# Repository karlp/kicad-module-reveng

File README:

Contains kicad projects used to generate rough 3d models for various modules.

The schematics are _very_ not clean, they're just enough to get all the right footprints so that kicad can autogenerate a nice 3d model for me.

Each directory should have it's own readme

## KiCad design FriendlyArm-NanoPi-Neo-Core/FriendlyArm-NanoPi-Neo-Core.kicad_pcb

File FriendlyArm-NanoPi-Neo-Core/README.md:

## physical model of NanoPi Neo Core

A "schematic" and "layout" that is _only_ intended to capture the
physical properties, making it easier to 3d model.

The usb connector and sd card connector and leds are all
not entirely _correct_ but are representitive, and placed appropriately.

Sources:
http://wiki.friendlyarm.com/wiki/index.php/NanoPi_NEO_Core

## Preview 
Examples of how it looks right now....

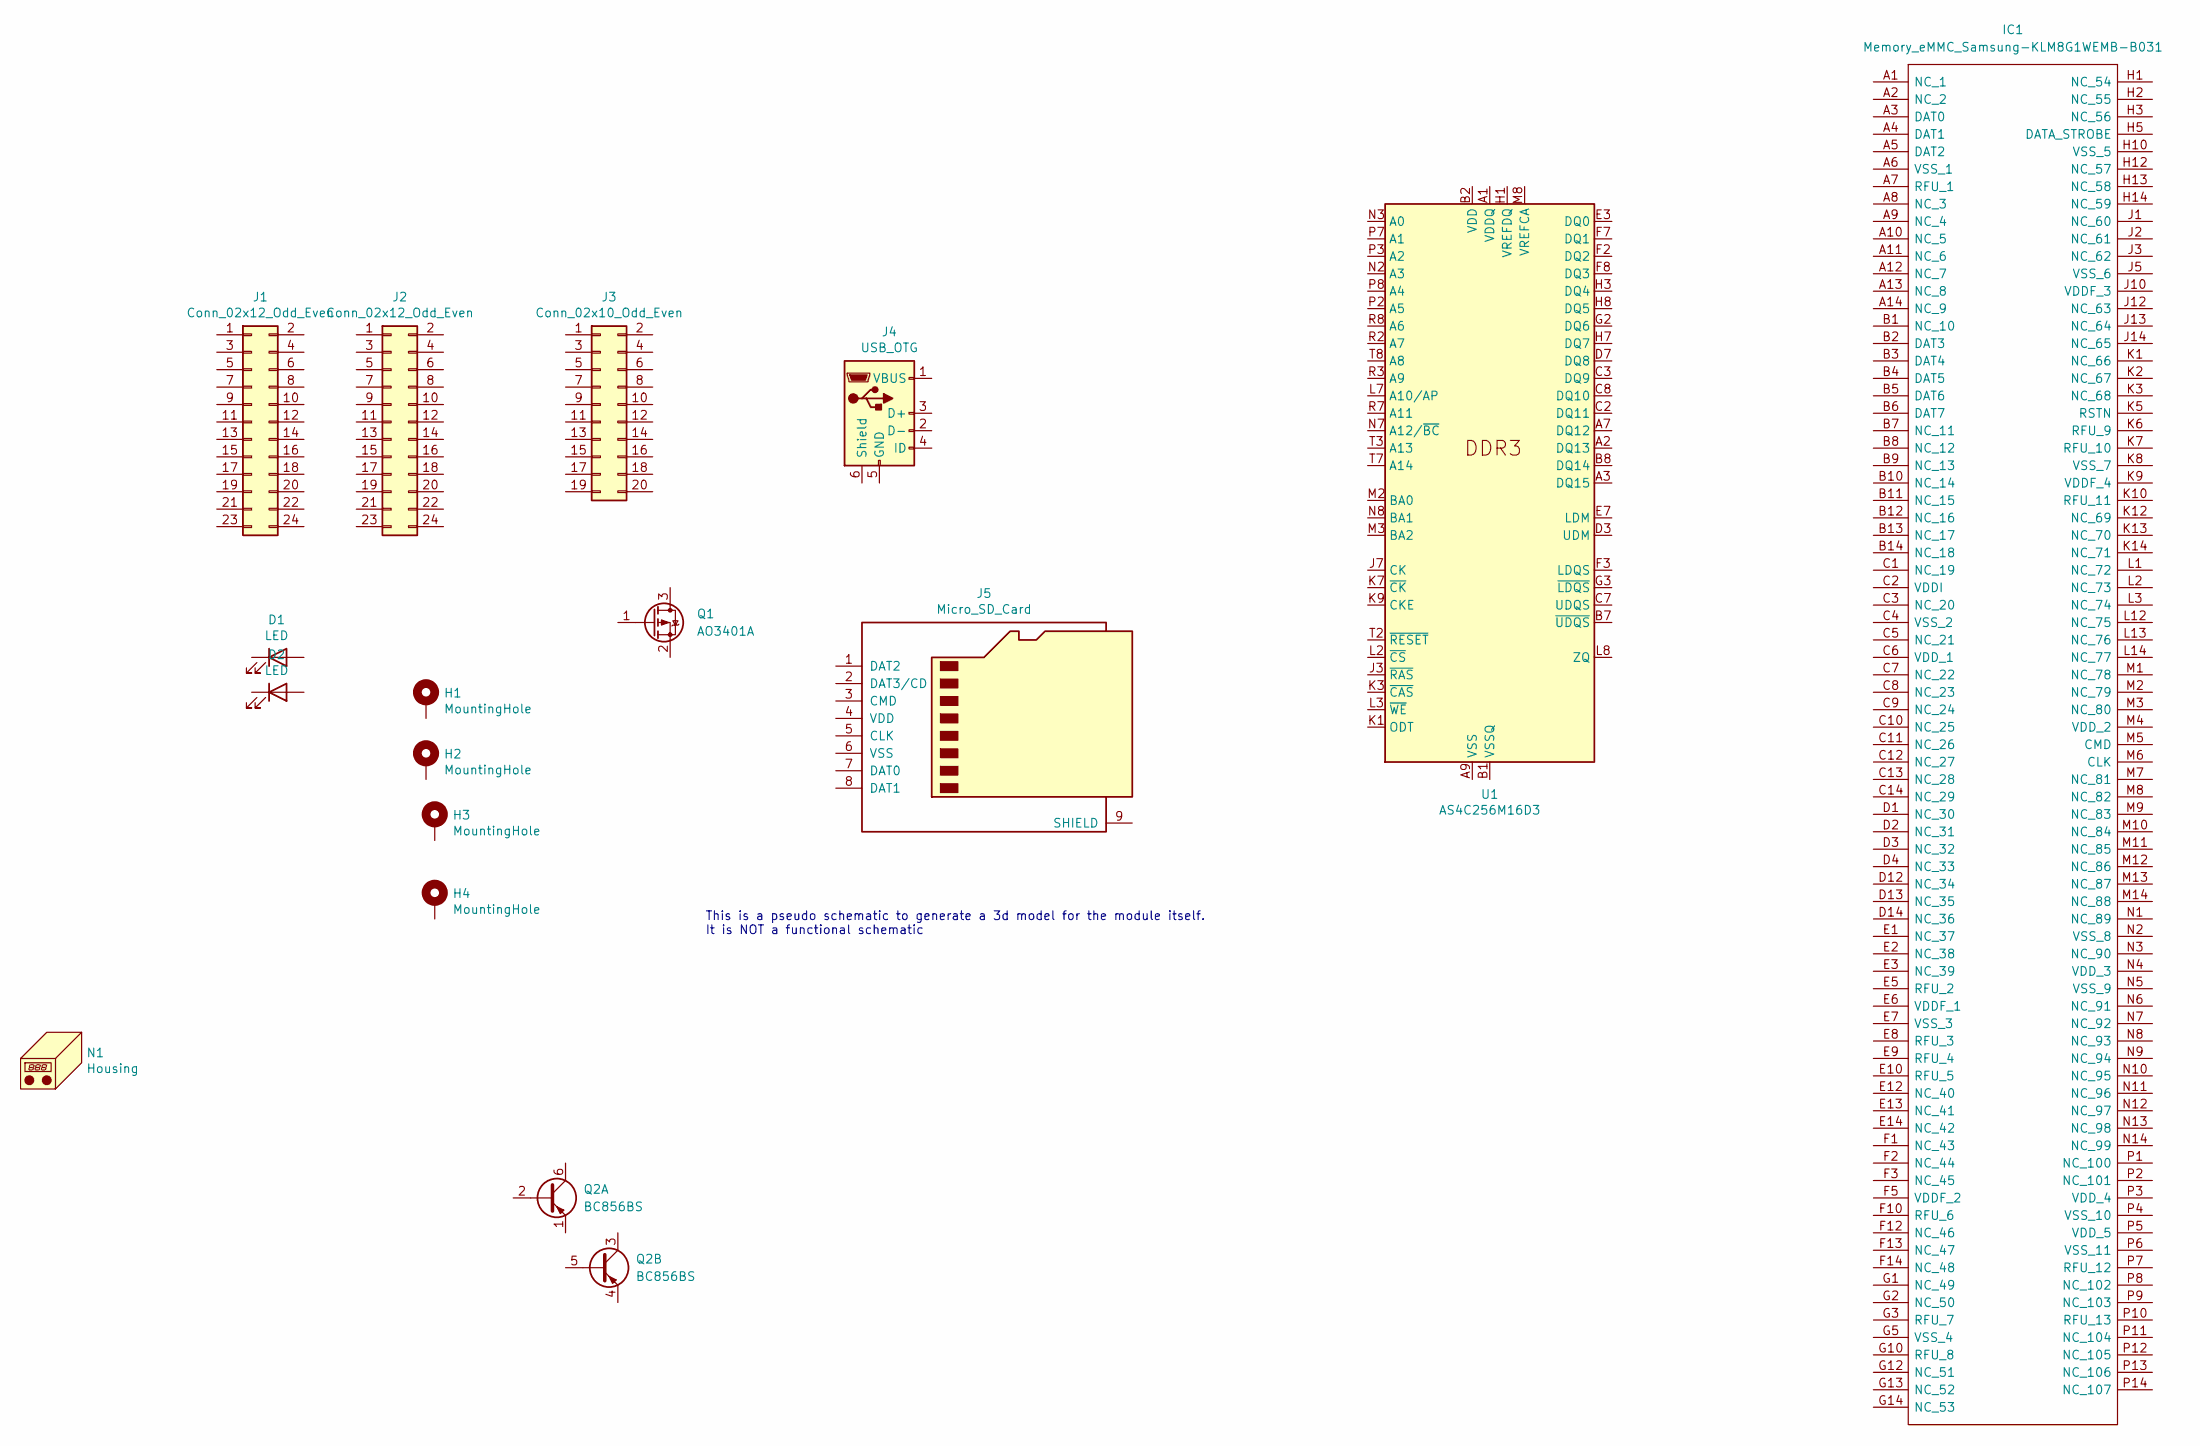
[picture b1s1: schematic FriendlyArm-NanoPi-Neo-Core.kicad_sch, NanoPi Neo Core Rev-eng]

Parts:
D1, D2: LED; LED_0603_1608Metric
H1, H2, H3, H4: MountingHole; MountingHole_3mm_Pad
IC1: Memory_eMMC_Samsung-KLM8G1WEMB-B031; BGA153_P0.5mm_14X14_11.5x13.0mm_h0.8mm_Samsung_eMMC; Manufacturer_Part_Number KLM8G1WEMB-B031
J1, J2: Conn_02x12_Odd_Even; PinHeader_2x12_P2.54mm_Vertical
J3: Conn_02x10_Odd_Even; PinHeader_2x10_P2.54mm_Vertical
J4: USB_OTG; USB_Micro-B_Molex_47346-0001
J5: Micro_SD_Card; microSD_HC_Hirose_DM3D-SF
N1: Housing; BGA-256_14.0x14.0mm_Layout16x16_P0.8mm_Ball0.45mm_Pad0.32mm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
Q1: AO3401A; SOT-23
Q2: BC856BS; SOT-363_SC-70-6
U1: AS4C256M16D3; BGA-96_9.0x13.0mm_Layout2x3x16_P0.8mm

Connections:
unnamed: U1.A1 (VDDQ), U1.A8 (VDDQ), U1.C1 (VDDQ), U1.C9 (VDDQ), U1.D2 (VDDQ), U1.E9 (VDDQ), U1.F1 (VDDQ), U1.H2 (VDDQ), U1.H9 (VDDQ)
unnamed: U1.A9 (VSS), U1.B3 (VSS), U1.E1 (VSS), U1.G8 (VSS), U1.J2 (VSS), U1.J8 (VSS), U1.M1 (VSS), U1.M9 (VSS), U1.P1 (VSS), U1.P9 (VSS), U1.T1 (VSS), U1.T9 (VSS)
unnamed: U1.B1 (VSSQ), U1.B9 (VSSQ), U1.D1 (VSSQ), U1.D8 (VSSQ), U1.E2 (VSSQ), U1.E8 (VSSQ), U1.F9 (VSSQ), U1.G1 (VSSQ), U1.G9 (VSSQ)
unnamed: U1.B2 (VDD), U1.D9 (VDD), U1.G7 (VDD), U1.K2 (VDD), U1.K8 (VDD), U1.N1 (VDD), U1.N9 (VDD), U1.R1 (VDD), U1.R9 (VDD)

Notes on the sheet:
This is a pseudo schematic to generate a 3d model for the module itself. It is NOT a functional schematic

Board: 2 copper layers, 16 parts (5 on the bottom side), 4 nets, no tracks yet.

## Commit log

2018-11-11 initial draft commit
2018-11-11 include example render and current exported .step
2018-11-11 fix markdown style
2018-11-17 ignore more freecad/librecad temp files
2018-11-17 root readme too please
2018-11-17 Start ona friendly arm nanopi core module
    having problems making a step export :(
2018-11-17 move to subdir and add gitignore
2018-11-18 nanopi neo core: "finished" model
2018-11-18 neo core: add images
2018-11-18 fix image links :)
2021-03-02 nanopi core: update to kicad 5.99x project files
2021-03-02 superseded by by kicad5.99 files
2021-03-02 nanopi-core: completely overhaul model
    Properly numerically align, place all big bgas, label headers
2021-03-02 nanopi core: replace with correct new model
    pins up as shipped by default, and with step manually edited to include
    product details.
2021-03-02 git ignore more droppings
2021-03-02 feasycom bw112d (rtl8723d module)
2021-03-02 nanopi-core: update images to match latest corrected model
2022-10-20 nano-pi neo core: fix emmc, add parts on edge
    There's a fairly high sot23 part rigth on the edge that you may want to
    be careful with if you're cramming things....
    Also, this uses a proper model for the emmc that is positioned better
    and has the right heights.
